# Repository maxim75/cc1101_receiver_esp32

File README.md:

# CC1101 + nRF24L01 Dual RF Receiver (ESP32-S3)

ESP32-S3 firmware that receives RF packets from two radios simultaneously and displays decoded data on an SH1107 128×128 OLED and serial monitor.

- **CC1101** — 433.92 MHz OOK packets from an ATtiny3226 transmitter (ELECHOUSE SmartRC-compatible protocol)
- **nRF24L01** — 2.4 GHz packets at 250 kbps, PA MAX

## Hardware

**Board:** ESP32-S3-DevKitC-1 (16 MB flash, PSRAM, native USB CDC)

### Wiring

| Peripheral | Signal | GPIO |
|------------|--------|------|
| CC1101     | SCK    | 12 (FSPI/SPI2) |
|            | MOSI   | 11 |
|            | MISO   | 13 |
|            | CSN    | 10 |
|            | GDO0   | 2 (interrupt) |
| nRF24L01   | SCK    | 14 (HSPI/SPI3) |
|            | MOSI   | 1 |
|            | MISO   | 21 |
|            | CSN    | 6 |
|            | CE     | 5 |
|            | IRQ    | 4 (wired, not used) |
| SH1107     | SDA    | 8 |
|            | SCL    | 9 |

All peripherals: VCC → 3.3 V, GND → GND

## Build & Flash

Requires [PlatformIO](https://platformio.org/).

```bash
# Build only
pio run

# Flash
pio run --target upload

# Flash and open serial monitor
pio run --target upload && pio device monitor

# Serial monitor only (115200 baud)
pio device monitor
```

## Dependencies

Managed automatically by PlatformIO:

| Library | Purpose |
|---------|---------|
| `jgromes/RadioLib` | CC1101 driver |
| `nrf24/RF24` | nRF24L01 driver |
| `olikraus/U8g2` | SH1107 OLED driver |
| `bblanchon/ArduinoJson` | JSON (available, not yet used) |

## How It Works

All firmware lives in `src/main.cpp`.

**CC1101** — interrupt-driven: GDO0 RISING edge sets a flag; `loop()` reads the packet with RadioLib, re-arms `startReceive()`, then calls `getRSSI()`.

**nRF24L01** — polled: `loop()` calls `nrf24.available()` each iteration; no re-arm needed.

Both radios share the same `PacketInfo` struct (`source`, hex, ASCII, RSSI, count). After each packet the OLED and serial monitor are updated; the OLED header shows which radio sourced the last packet.

**SPI:** CC1101 on FSPI (`SPI`), nRF24 on HSPI (`hspi`) — separate buses, no CS conflicts.

## Serial Output

Each received packet is logged at 115200 baud:

```
[CC1101] #1 | RSSI: -72 dBm | HEX: D3 91 04 AB CD | ASCII: ...
[nRF24]  #2 | HEX: 48 65 6C 6C 6F     | ASCII: Hello
```

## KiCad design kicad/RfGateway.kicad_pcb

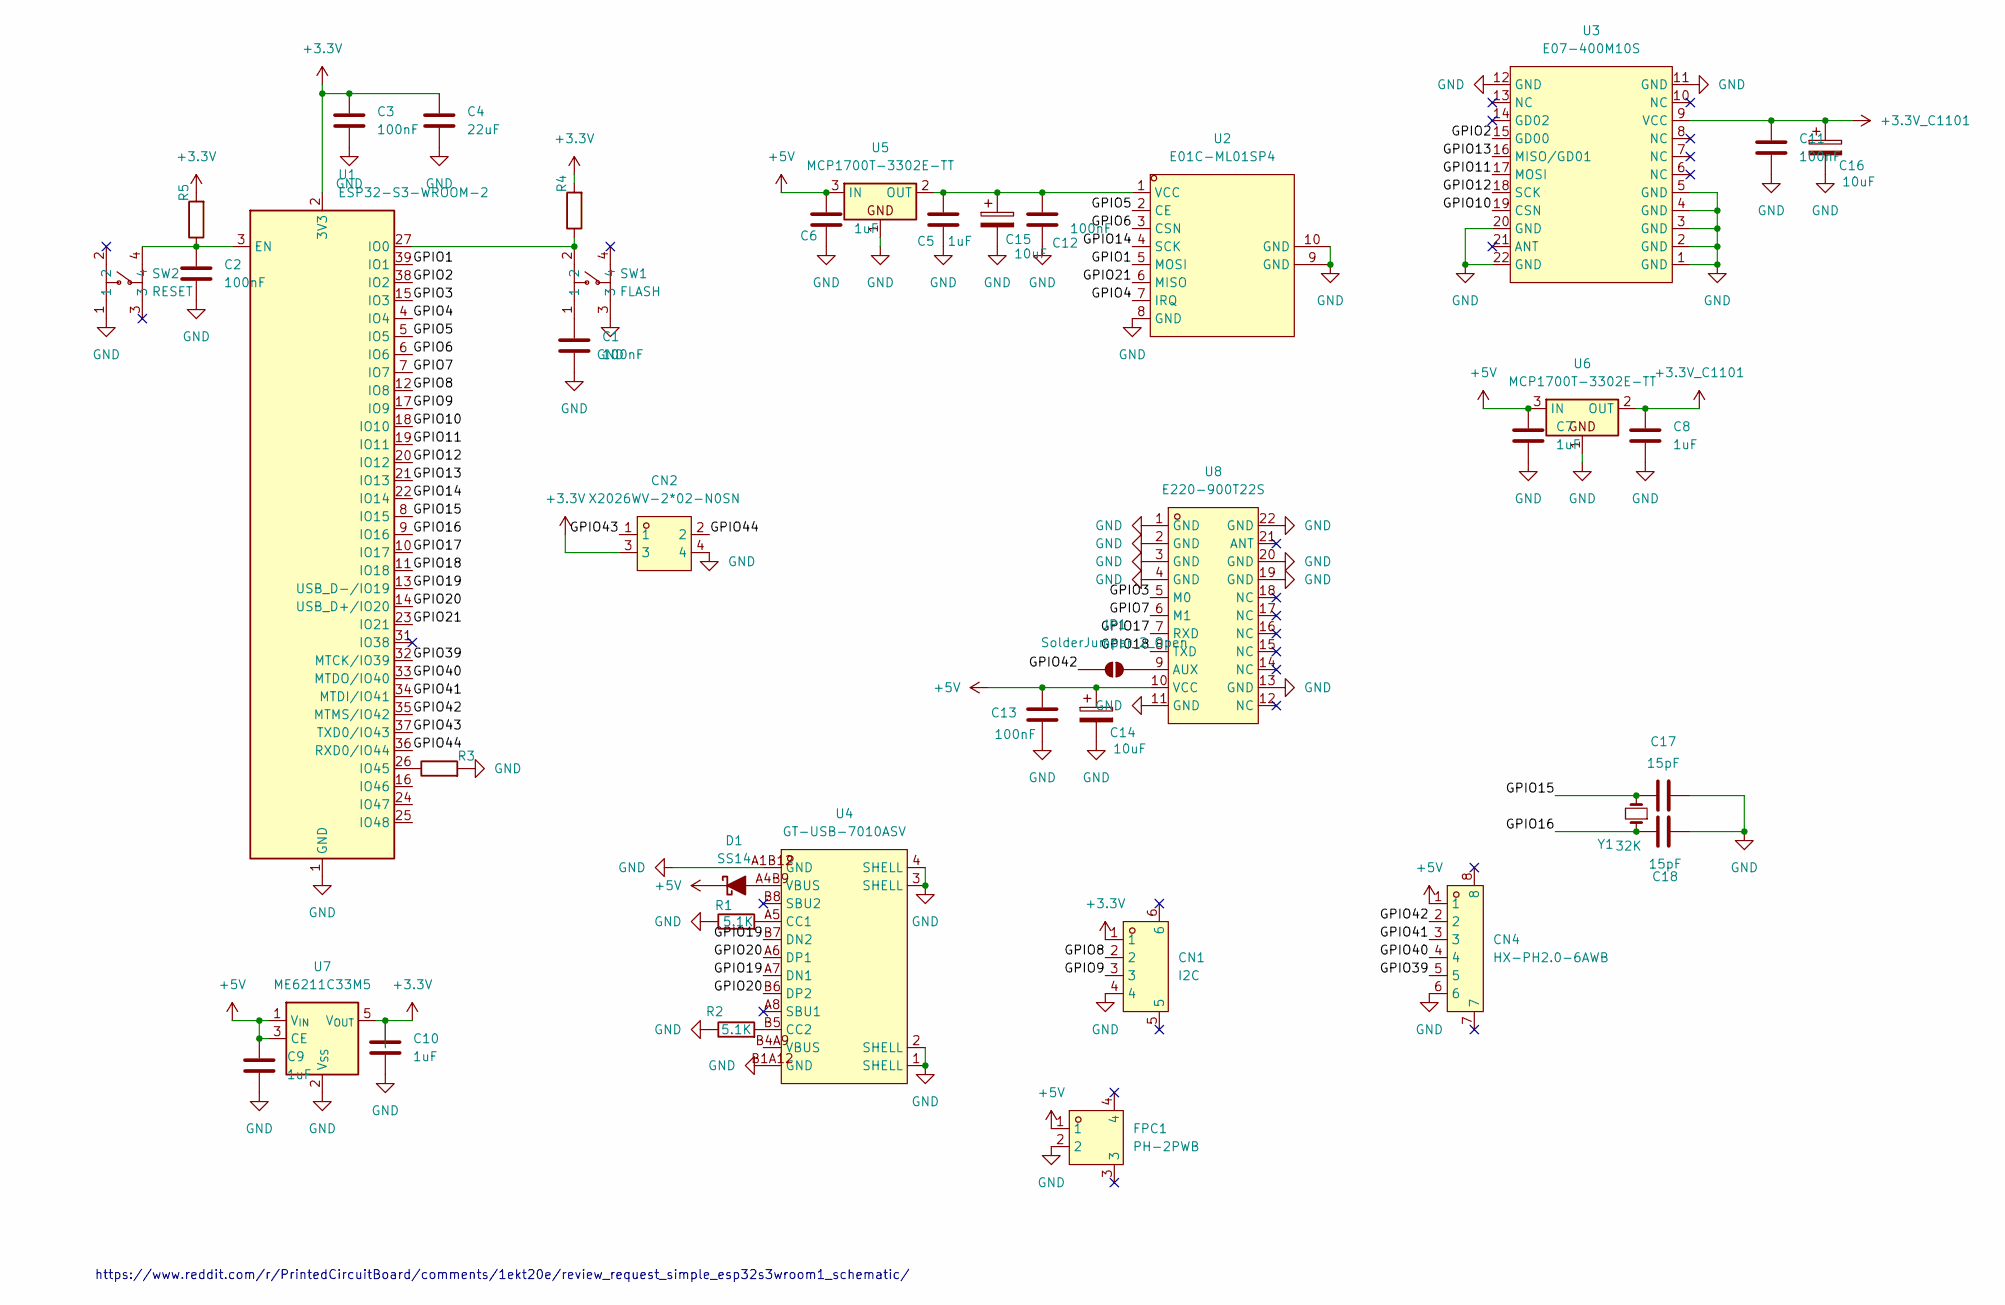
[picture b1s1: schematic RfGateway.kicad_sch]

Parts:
C1, C2, C3, C11, C12, C13: 100nF; C_0805_2012Metric_Pad1.18x1.45mm_HandSolder
C4: 22uF; C_0805_2012Metric_Pad1.18x1.45mm_HandSolder
C5, C6, C7, C8, C9, C10: 1uF; C_0805_2012Metric_Pad1.18x1.45mm_HandSolder
C14, C15, C16: 10uF; CP_Radial_D5.0mm_P2.00mm
C17, C18: 15pF; C_0805_2012Metric_Pad1.18x1.45mm_HandSolder
CN1: I2C; CONN-SMD_HCZZ0451-4; LCSC Part C7433650
CN2: X2026WV-2*02-N0SN; CONN-TH_X2026WV-2X02-N0SN; LCSC Part C406181
CN4: HX-PH2.0-6AWB; CONN-SMD_HX-PH2.0-6AWB; LCSC Part C52016430
D1: SS14; D_SMA
FPC1: PH-2PWB; FPC-SMD_2P-P2.00_DEALON_PH-2PWB; LCSC Part C2905019
JP1: SolderJumper_2_Open; SolderJumper-2_P1.3mm_Open_Pad1.0x1.5mm
R1, R2: 5.1K; R_0805_2012Metric_Pad1.20x1.40mm_HandSolder
R3, R4, R5: 10K; R_0805_2012Metric_Pad1.20x1.40mm_HandSolder
SW1: FLASH; SW-SMD_4P-L4.5-W4.5-P3.00-LS7.5; LCSC Part C22375348
SW2: RESET; SW-SMD_4P-L4.5-W4.5-P3.00-LS7.5; LCSC Part C22375348
U1: ESP32-S3-WROOM-2
U2: E01C-ML01SP4; COMM-SMD_E01C-ML01SP4; LCSC Part C2965508
U3: E07-400M10S; COMM-SMD_E07-400M10S; LCSC Part C2965513
U4: GT-USB-7010ASV; USB-C-SMD_G-SWITCH_GT-USB-7010ASV; LCSC Part C2988369
U5, U6: MCP1700T-3302E-TT; SOT-23
U7: ME6211C33M5; SOT-23-5
U8: E220-900T22S; WIRELM-SMD_E220-900T22S; LCSC Part C970285
Y1: 32K; Crystal_AT310_D3.0mm_L10.0mm_Horizontal

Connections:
+3.3V: C3.1, C4.1, C10.1, CN1.1, CN2.3, R4.2, R5.2, U1.2 (3V3), U7.5 (V_{OUT})
+3.3V_C1101: C8.1, C11.1, C16.1, U3.9 (VCC), U6.2 (OUT)
+5V: C6.1, C7.1, C9.1, C13.1, C14.1, CN4.1, D1.1 (K), FPC1.1, U5.3 (IN), U6.3 (IN), U7.1 (V_{IN}), U7.3 (CE), U8.10 (VCC)
/GPIO1: U1.39 (IO1), U2.5 (MOSI)
/GPIO2: U1.38 (IO2), U3.15 (GD00)
/GPIO3: U1.15 (IO3), U8.5 (M0)
/GPIO4: U1.4 (IO4), U2.7 (IRQ)
/GPIO5: U1.5 (IO5), U2.2 (CE)
/GPIO6: U1.6 (IO6), U2.3 (CSN)
/GPIO7: U1.7 (IO7), U8.6 (M1)
/GPIO8: CN1.2, U1.12 (IO8)
/GPIO9: CN1.3, U1.17 (IO9)
/GPIO10: U1.18 (IO10), U3.19 (CSN)
/GPIO11: U1.19 (IO11), U3.17 (MOSI)
/GPIO12: U1.20 (IO12), U3.18 (SCK)
/GPIO13: U1.21 (IO13), U3.16 (MISO/GD01)
/GPIO14: U1.22 (IO14), U2.4 (SCK)
/GPIO15: C17.1, U1.8 (IO15), Y1.2
/GPIO16: C18.1, U1.9 (IO16), Y1.1
/GPIO17: U1.10 (IO17), U8.7 (RXD)
/GPIO18: U1.11 (IO18), U8.8 (TXD)
/GPIO19: U1.13 (USB_D-/IO19), U4.A7 (DN1), U4.B7 (DN2)
/GPIO20: U1.14 (USB_D+/IO20), U4.A6 (DP1), U4.B6 (DP2)
/GPIO21: U1.23 (IO21), U2.6 (MISO)
/GPIO39: CN4.5, U1.32 (MTCK/IO39)
/GPIO40: CN4.4, U1.33 (MTDO/IO40)
/GPIO41: CN4.3, U1.34 (MTDI/IO41)
/GPIO42: CN4.2, JP1.1 (A), U1.35 (MTMS/IO42)
/GPIO43: CN2.1, U1.37 (TXD0/IO43)
/GPIO44: CN2.2, U1.36 (RXD0/IO44)
GND: C1.2, C2.2, C3.2, C4.2, C5.2, C6.2, C7.2, C8.2, C9.2, C10.2, C11.2, C12.2, C13.2, C14.2, C15.2, C16.2, C17.2, C18.2, CN1.4, CN2.4, CN4.6, FPC1.2, R1.1, R2.1, R3.2, SW1.3, SW2.1, U1.1 (GND), U1.40 (GND), U1.41 (GND), U2.8 (GND), U2.9 (GND), U2.10 (GND), U3.1 (GND), U3.2 (GND), U3.3 (GND), U3.4 (GND), U3.5 (GND), U3.11 (GND), U3.12 (GND), U3.20 (GND), U3.22 (GND), U4.1 (SHELL), U4.2 (SHELL), U4.3 (SHELL), U4.4 (SHELL), U4.A1B12 (GND), U4.B1A12 (GND), U5.1, U6.1, U7.2 (V_{SS}), U8.1 (GND), U8.2 (GND), U8.3 (GND), U8.4 (GND), U8.11 (GND), U8.13 (GND), U8.19 (GND), U8.20 (GND), U8.22 (GND)
unnamed: C1.1, SW1.1
unnamed: D1.2 (A), U4.A4B9 (VBUS)
unnamed: JP1.2 (B), U8.9 (AUX)
unnamed: C2.1, R5.1, SW2.4, U1.3 (EN)
unnamed: R4.1, SW1.2, U1.27 (IO0)
unnamed: R3.1, U1.26 (IO45)
unnamed: C5.1, C12.1, C15.1, U2.1 (VCC), U5.2 (OUT)
unnamed: R1.2, U4.A5 (CC1)
unnamed: R2.2, U4.B5 (CC2)

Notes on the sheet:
https://www.reddit.com/r/PrintedCircuitBoard/comments/1ekt20e/review_request_simple_esp32s3wroom1_schematic/

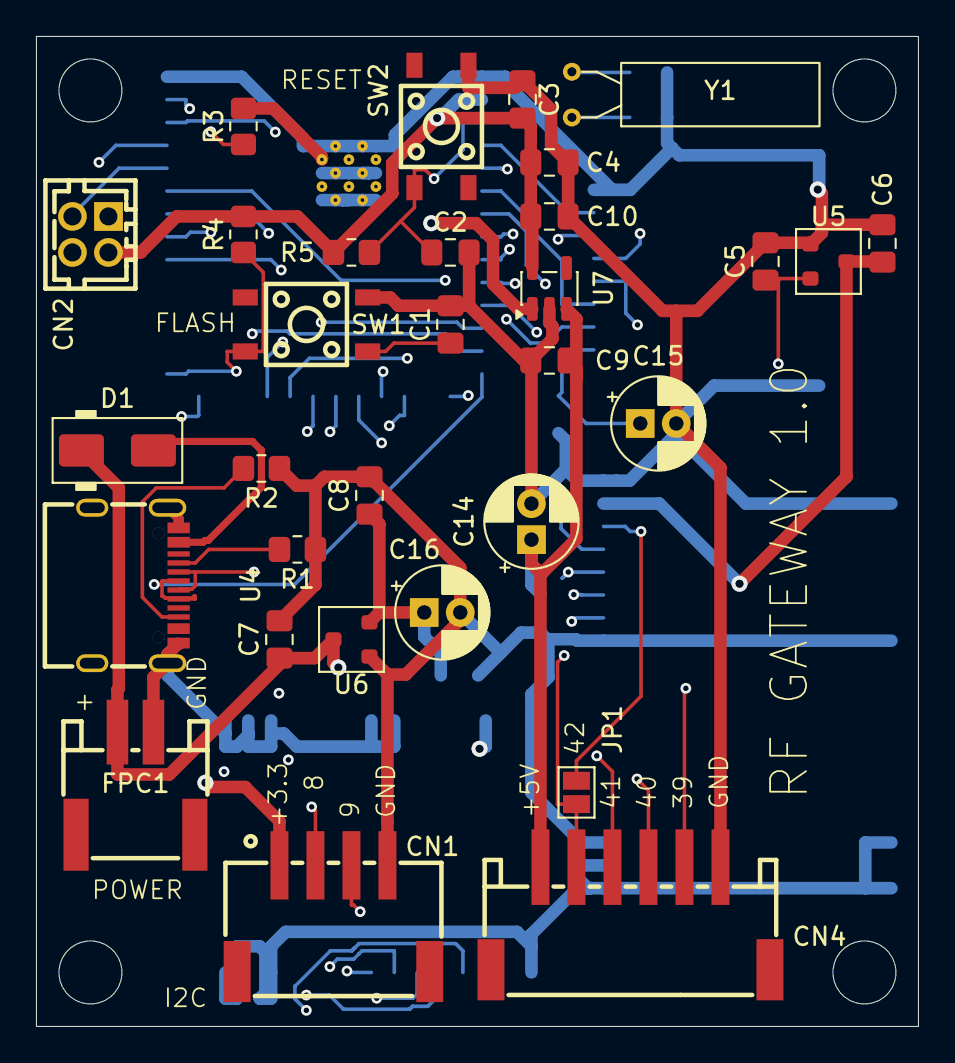
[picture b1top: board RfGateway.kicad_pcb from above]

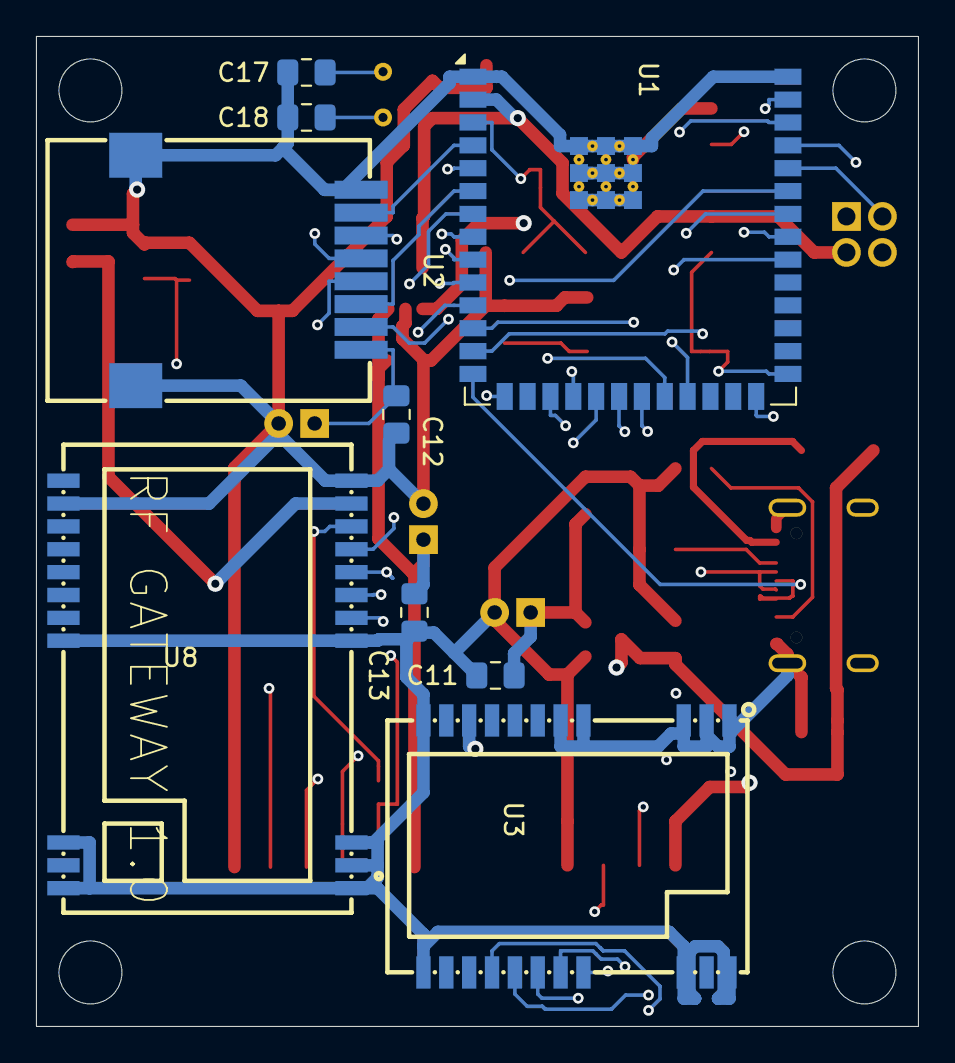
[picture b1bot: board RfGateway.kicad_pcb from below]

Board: 4 copper layers, 49.0 x 55.0 mm, 40 parts (9 on the bottom side), 40 nets.

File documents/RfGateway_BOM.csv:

"Reference","Qty","Value","DNP","Exclude from BOM","Exclude from Board","Footprint","Datasheet"
"C1,C2,C3,C11,C12,C13","6","100nF","","","","Capacitor_SMD:C_0805_2012Metric_Pad1.18x1.45mm_HandSolder",""
"C4","1","22uF","","","","Capacitor_SMD:C_0805_2012Metric_Pad1.18x1.45mm_HandSolder",""
"C5,C6,C7,C8,C9,C10","6","1uF","","","","Capacitor_SMD:C_0805_2012Metric_Pad1.18x1.45mm_HandSolder",""
"C14,C15,C16","3","10uF","","","","PCM_Capacitor_THT_AKL:CP_Radial_D5.0mm_P2.00mm",""
"C17,C18","2","15pF","","","","Capacitor_SMD:C_0805_2012Metric_Pad1.18x1.45mm_HandSolder",""
"CN1","1","I2C","","","","easyeda2kicad:CONN-SMD_HCZZ0451-4",""
"CN2","1","X2026WV-2*02-N0SN","","","","easyeda2kicad:CONN-TH_X2026WV-2X02-N0SN","https://lcsc.com/product-detail/Wire-To-Board-Wire-To-Wire-C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"
"CN4","1","HX-PH2.0-6AWB","","","","easyeda2kicad:CONN-SMD_HX-PH2.0-6AWB",""
"D1","1","SS14","","","","PCM_Diode_SMD_AKL:D_SMA","https://www.tme.eu/Document/39e1c2d2c354f63d74e9a2edb2156b4b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"
"FPC1","1","PH-2PWB","","","","easyeda2kicad:FPC-SMD_2P-P2.00_DEALON_PH-2PWB",""
"R1,R2","2","5.1K","","","","Resistor_SMD:R_0805_2012Metric_Pad1.20x1.40mm_HandSolder",""
"R3,R4,R5","3","10K","","","","Resistor_SMD:R_0805_2012Metric_Pad1.20x1.40mm_HandSolder",""
"SW1","1","FLASH","","","","easyeda2kicad:SW-SMD_4P-L4.5-W4.5-P3.00-LS7.5",""
"SW2","1","RESET","","","","easyeda2kicad:SW-SMD_4P-L4.5-W4.5-P3.00-LS7.5",""
"U1","1","ESP32-S3-WROOM-2","","","","RF_Module:ESP32-S3-WROOM-2","https://www.espressif.com/sites/default/files/documentation/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"
"U2","1","E01C-ML01SP4","","","","easyeda2kicad:COMM-SMD_E01C-ML01SP4",""
"U3","1","E07-400M10S","","","","easyeda2kicad:COMM-SMD_E07-400M10S",""
"U4","1","GT-USB-7010ASV","","","","easyeda2kicad:USB-C-SMD_G-SWITCH_GT-USB-7010ASV",""
"U5,U6","2","MCP1700T-3302E-TT","","","","PCM_Package_TO_SOT_SMD_AKL:SOT-23","https://ww1.microchip.com/downloads/en/DeviceDoc/MCP1700-Low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"
"U7","1","ME6211C33M5","","","","Package_TO_SOT_SMD:SOT-23-5","https://www.lcsc.com/datasheet/lcsc_datasheet_2304140030_MIC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"
"U8","1","E220-900T22S","","","","easyeda2kicad:WIRELM-SMD_E220-900T22S","https://lcsc.com/product-detail/Wireless-Modules_Chengdu-Eby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"
"Y1","1","32K","","","","Crystal:Crystal_AT310_D3.0mm_L10.0mm_Horizontal",""

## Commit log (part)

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2026-03-08 init
2026-03-08 decode PT22620
2026-03-23 receive message from attiny
2026-04-28 Update main and add receiver source files
2026-04-28 Switch to RadioLib for CC1101 receive
2026-04-28 Add SH1106 OLED display support via U8g2
2026-04-28 Refactor: namespaces, PacketInfo struct, helper functions
2026-04-29 Switch nRF24 receiver to RF24 library
2026-04-29 Expand CLAUDE guidance with coding guardrails
2026-04-29 Separate CC1101 and nRF24L01 onto dedicated SPI buses
    - Migrate CC1101 to FSPI (SPI2): GPIO 11/12/13 with CS on GPIO 10
    - Migrate nRF24L01 to HSPI (SPI3): GPIO 14/15/16 with CS on GPIO 6
    - Add SPIClass hspi instance and initialize in setup()
    - Update CLAUDE.md wiring table and architecture notes
    - Add VS Code extension recommendations
2026-04-29 fix: read actual nRF24 payload length via getDynamicPayloadSize/getPayloadSize
    Agent-Logs-Url: https://github.com/maxim75/cc1101_receiver_esp32/sessions/2e9f2deb-e697-4acf-9f65-a31d00ca5fc1
2026-04-29 fix: add uint8_t cast on sizeof(buf) in nRF24 payload length guard
    Agent-Logs-Url: https://github.com/maxim75/cc1101_receiver_esp32/sessions/2e9f2deb-e697-4acf-9f65-a31d00ca5fc1
2026-04-29 docs: update CLAUDE.md architecture notes for RF24 polling implementation
    Agent-Logs-Url: https://github.com/maxim75/cc1101_receiver_esp32/sessions/e624d645-7fc8-45b2-a897-f423918a2328
2026-04-30 Update nRF24 SPI pins to GPIO1/GPIO21
